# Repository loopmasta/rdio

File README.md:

# rdio

**rdio** turns your iPhone into a VHF/UHF radio. It connects to one or more ESP32-powered devices equipped with radio modules over Wi-Fi. Listen to transmissions, talk with push-to-talk, save your favourite channels and repeaters, and exchange APRS messages in a familiar chat-style interface.

<table>
  <tr>
    <td align="center"></td>
    <td align="center"></td>
    <td align="center"></td>
    <td align="center"></td>
    <td align="center"></td>
  </tr>
  <tr>
    <td align="center">Main screen</td>
    <td align="center">Transmit</td>
    <td align="center">APRS chat</td>
    <td align="center">Channel editor</td>
    <td align="center">Settings</td>
  </tr>
</table>

## How it works

- The ESP32 opens its own Wi-Fi network (or joins one you configure). The phone connects to it and talks to the radio over a WebSocket. Radios on a shared network are found automatically (Bonjour), so one app can control several of them.
- Receive audio goes from the radio to the phone as 16 kHz mono PCM. Transmit audio goes the other way while you hold the push-to-talk button.
- The module is tuned, squelched and keyed by the ESP32 through its UART and PTT lines, and a further line sets its transmit power.
- Bluetooth is not used.

## Features

- **Receive and transmit** in the selected band (VHF 134–174 MHz or UHF 400–480 MHz).
- **Channel list** with simplex and duplex (repeater) entries, shift direction and offset, CTCSS transmit and receive tones, and a 1750 Hz tone burst. Reorder by dragging, swipe to edit or delete.
- **APRS** on 1200 baud AFSK: the app decodes received packets (positions, Mic-E, messages, status) on APRS channels, shows them as a chat with distance and a link to Maps, links call signs to QRZ.com. You can also send: type a message in the chat to a call sign or to CQ. Messages to a station are repeated until it acknowledges them, the app acknowledges messages addressed to you, and everything is sent only while the channel is clear. A periodic position beacon is available too.
- **Several radios:** each radio announces itself on the network as a Bonjour service (`_rdio._tcp`, with its name, module type and firmware version). The app lists the radios it finds in Settings → Radio and switches between them with one tap. Give every radio its own name (Settings → Radio Name), because the name is also its Wi-Fi and host name.
- **Phone microphone chain** with a compressor and a mic level setting, the radio limits the transmit level so the deviation cannot be exceeded.
- **Native iOS design**: system controls, Light and Dark Mode, Dynamic Type, VoiceOver, haptics, no navigation bar.
- **Transmit safety**: the app only transmits inside the selected band, and the firmware releases the push-to-talk line when the connection drops, when no audio arrives, and after 120 seconds. Only one client can transmit.
- **Transmit power:** high (1 W) or low (0.5 W) with a switch in Settings → Radio. The radio remembers the choice; low power draws about half as much from the battery while transmitting.
- Firmware updates over Wi-Fi.

## Status

Working on a real radio: receive, transmit, channel handling, tones, tone burst, APRS decoding, and the APRS position beacon (tested over the air).

Not done yet: a scan function in the app.

The carrier board below is designed and routed; its [README](hardware/radio/README.md) lists the checks it passes and what is still to be verified at the bench. The harmonic filters below are **designed but not built or measured yet**. They are simulated only; check them with a NanoVNA before relying on them.

## Hardware

Everything is KiCad 10 and is generated by scripts, so the boards can be rebuilt and changed in code.

### Carrier board

A 57.4 × 26.0 mm two-layer board for an ESP32 38-pin DevKit (NodeMCU-32S style) and an SA818S / DRA818 module. The DevKit sits on top of the board plugged onto two 19-pin headers soldered into it from the bottom, the radio module sits on the bottom side, and an SMA jack on the end opposite the DevKit's USB port carries the antenna signal on a short track. There are two footprints for the jack, an edge-mount one and a right-angle one on top of the board; you fit one of them. Design files, parts and notes: [hardware/radio/README.md](hardware/radio/README.md).

<table>
  <tr>
    <td align="center"></td>
    <td align="center"></td>
  </tr>
  <tr>
    <td align="center">Top: DevKit (the audio and supply parts are under it), SMA jack</td>
    <td align="center">Bottom: radio module, SMA jack, DevKit pin rows</td>
  </tr>
</table>

| Function | ESP32 pin |
|---|---|
| Module UART (RX / TX) | GPIO16 / GPIO17 |
| PTT (low = transmit) | GPIO21, with a 10 k pull-up to 3.3 V |
| Squelch in | GPIO22 |
| High / low power | GPIO19 (open drain: the firmware pulls it low for 0.5 W and releases it for 1 W; it never drives it high) |
| RX audio in (ADC) | GPIO34, through a coupling capacitor and a 1.65 V bias divider |
| TX audio out | GPIO25, through an attenuator of about 1/100 |
| Power down | none: the module's power-down pin is tied to 3.3 V |

- The module's supply pin is fed from the DevKit's VIN pin (5 V from its USB-C) through a 0 Ω link, with a 220 µF and a 100 nF capacitor next to the module. The module draws up to 0.75 A while transmitting at high power, so use a 5 V source that can deliver at least 1 A (2 A is better) and check the voltage on the DevKit's VIN pin before the first power-up.
- Pin numbers and the antenna end are printed on the bottom silkscreen inside the module outline, to help with placing it.
- Connect an antenna or a dummy load before the first transmission and start the bench tests at low power. Details and the open points: [hardware/radio/README.md](hardware/radio/README.md).

### Harmonic filters (2 m and 70 cm)

Two small all-SMD low-pass filters (7th-order Chebyshev, 0.1 dB ripple, 50 Ω) that go between the board's SMA jack and the antenna and cut the radio module's harmonics. Details, simulation and parts notes: [hardware/filter/README.md](hardware/filter/README.md).

<table>
  <tr>
    <td align="center"></td>
    <td align="center"></td>
  </tr>
  <tr>
    <td align="center">2 m, 144–146 MHz</td>
    <td align="center">70 cm, 430–440 MHz</td>
  </tr>
</table>

| | 2 m | 70 cm |
|---|---|---|
| Passband | 144–146 MHz | 430–440 MHz |
| Insertion loss (simulated) | 0.56 dB | 0.50 dB |
| 2nd harmonic (simulated) | 52 dB down | 63 dB down |
| Board size | 38.6 × 12.4 mm | 35.0 × 12.4 mm |

### Ordering the boards

Gerber, drill, bill of materials and placement files for JLCPCB are in [hardware/jlcpcb/](hardware/jlcpcb/README.md): `radio/` for the carrier board and `filters/vhf`, `filters/uhf` for the filters. Check the LCSC part numbers in the bills of materials against JLCPCB's parts library before you order; the filter boards have none yet, because their inductors are still to be chosen. The electrolytic capacitors, the SMA connectors, the DevKit headers and the radio module are soldered by hand.

## Legal

Transmitting needs an amateur radio licence and must follow the rules that apply to you. The app limits the transmit frequency to the selected band, but you are responsible for staying within your licence and the local regulations.

**Privacy:** the app has no accounts, analytics or tracking. See the [privacy policy](https://loopmasta.github.io/rdio/privacy/).

## Repository contents

This repository lets a small group of testers order the hardware, build it and install the app, with no software knowledge or development tools. It holds the hardware design (`hardware/`), the screenshots (`docs/`) and this description.

The software is not included and does not need to be built:

- **iOS app:** the new version is not available yet, so there is no download link at the moment.
- **Firmware:** not published here. The web flasher has been removed, so there is no browser installer for the firmware at the moment.

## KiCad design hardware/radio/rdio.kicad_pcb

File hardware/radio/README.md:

# rdio carrier board

A 57.4 × 26.0 mm two-layer board that joins an ESP32 38-pin DevKit (NodeMCU-32S style) and an SA818S / DRA818 radio module. KiCad 10; the schematic and the board are generated by the scripts in [tools/](tools/README.md), so they can be changed in code.

- The DevKit sits **on top of** the thin carrier board, component side up. It plugs, with the 2.5 mm sockets built into it, onto two 19-pin headers (5 mm high) that are soldered into plated holes in the carrier from the bottom side.
- The radio module sits on the **bottom** side, between the two pin rows. It is mounted turned by 180° so that its antenna pad faces the SMA connector.
- The antenna connector is at the end where the DevKit's Wi-Fi antenna is, opposite the DevKit's USB port. The silkscreen says `ANT end (SMA side)` and `USB end (DevKit above)`. **Two connector footprints share that spot, and you fit one of them:**
  - **J2**, SMA edge connector (KooingTech SMA-KE, female, for 1.6 mm boards): sits on the board edge, the barrel points straight out of the board.
  - **J3**, right-angle SMA jack (BAT Wireless BWSMA-KWE-Z001, LCSC C496551, through hole): stands on the top side of the board, the barrel points out over the board edge. Its pads overlap those of J2, so never fit both.
- The small parts are on the top side, in the 7–8 mm gap between the carrier and the DevKit.

*3D render of the carrier board seen from the top (DevKit side). The DevKit and the radio module (on the bottom) are not shown. C8, FB1 and the J2 footprint are not fitted in the default build; C8 and FB1 are visible here.*

## Connections

| Module (SA818S) | Signal | ESP32 | Notes |
|---|---|---|---|
| 16 RXD | UART to the module | GPIO17 (UART2 TX) | 9600 baud, AT commands |
| 17 TXD | UART from the module | GPIO16 (UART2 RX) | connected directly, no series resistor |
| 5 PTT | transmit request | GPIO21 | low = transmit; **10 k pull-up to 3.3 V**, so a floating, crashed or resetting ESP32 means receive |
| 6 PD | power down | none | tied to 3.3 V: the module is always on |
| 7 H/L | power level | GPIO19 | open drain, low = low power (0.5 W), released = high power (1 W). **Never drive it high, never tie it to a supply.** |
| 1 SQ | squelch / carrier detect | GPIO22 | input, connected directly |
| 3 AF_OUT | receive audio | GPIO34 (ADC) | 1 µF coupling capacitor into a 100 k / 100 k divider (1.65 V bias) |
| 18 MIC_IN | transmit audio | GPIO25 (DAC) | 1 µF, then 100 k in series, 1 k to ground with 33 nF across it: about 1/100 attenuation, corner near 4.8 kHz |
| 12 ANT | antenna | SMA | 0.8 mm trace, drawn by hand |
| 8 VBAT, 9 / 10 GND | supply | | see Power |

GPIO26 and the other pins of the DevKit are not used.

## Power

- The module's VBAT comes from the DevKit's VIN pin (5 V from the DevKit's own USB-C) through R9, a 0 Ω link. The module accepts 3.3 to 5.5 V (the RF power is specified at 4.0 V).
- At the module: C6 100 µF, 16 V (6.3 mm can, 5.4 mm high; the board has the 6.3 × 5.8 mm footprint, which fits it; 220 µF was not available at 16 V) and C7 100 nF. On the 3.3 V side: C2 100 µF and C3 100 nF.
- **FB1 (ferrite bead) and C8 (100 µF) are not fitted.** To try them, fit both and remove R9: the bead keeps current steps of the module (power level change, PTT) away from the ESP32's regulator. Build without them first and see whether Wi-Fi still drops when the power level switches.
- The module draws about 60 mA receiving, 650–750 mA transmitting at high power and 450–550 mA at low power (datasheet). All of it passes through the DevKit's USB path and its VIN pin. Use a 5 V source that can deliver at least 1 A (2 A is better), and check the DevKit's input protection. USB 500 mA from a computer can brown out during a high-power transmission.
- Do not power the module from the DevKit's 3.3 V pin. Check the DevKit's behaviour before connecting USB and an external 5 V supply at the same time.

## Building and first power-up

1. Solder two 19-pin headers (5 mm high) into the carrier from the bottom side, then plug the DevKit onto them.
2. Place the SA818S on the bottom side with its antenna pad towards the SMA connector. Pin numbers 1 to 18 are printed inside the module outline, and an open ring marks the ring on the top of the module: put the module's ring over the board's ring.
3. Solder the antenna connector by hand: J2 (edge mount) or J3 (right angle on top), not both.
4. Connect a 50 Ω antenna or a dummy load **before the first transmission**, keep the antenna away from the DevKit's antenna and the audio wiring, and start the bench tests at low power. Transmitting needs the right amateur radio licence and an allowed frequency.

Gerber, drill, bill of materials and placement files for JLCPCB are in [../jlcpcb/radio/](../jlcpcb/README.md).

## Design status

The board is routed with Freerouting. KiCad's design rule check (with the project's rules, and also with 0.2 mm clearance, 0.3 mm copper-to-edge and 0.5 mm hole-to-hole) reports no unconnected items, no clearance errors, no shorts and no dangling tracks. What remains:

- the schematic symbol has a pin 11 (NC) that the footprint does not draw as a pad, which is harmless,
- the schematic check warns that the `VBAT` power symbol and the `Board` symbol library are not found, because the folder has no symbol library table,
- J2 (edge-mount SMA) has pads 0.25 mm from the board edge by design; it is not fitted in the default build.

## Still to verify at the bench

1. The typical-application schematic on pages 4 and 5 of the datasheet (the coupling into MIC_IN and the bias on AF_OUT) against the values above.
2. The idle and active voltage levels of pin 1.
3. The AF_OUT amplitude (peak or peak to peak) at each module volume setting.
4. The MIC_IN impedance, then change R4 (1 k) so that a 1750 Hz tone gives the right deviation (about 3 kHz), checked on a receiver or an SDR.

## Known limitations

- The antenna on the SMA connector is at the same end as the DevKit's Wi-Fi antenna, so a whip on the connector sits a few centimetres from it. A short coax pigtail, or an antenna mounted away from the board, helps more than any copper.
- Two RF filters were left out on purpose: 47–100 pF across R4 (2.4 GHz pickup into MIC_IN) and small series resistors and capacitors on the control lines (433 MHz pickup). The circuit is as shown.
- The 3D models are simple placeholders, not accurate models.

More details (footprints, the SMA connector, the shielding by copper pours, and a 4-layer variant): [design-notes.md](design-notes.md).

## Files

| File | What it is |
|---|---|
| `rdio.kicad_pro`, `rdio.kicad_sch`, `rdio.kicad_pcb` | the KiCad project, schematic and board |
| `rdio_schematic.pdf` | the schematic as a PDF |
| `rdio.pretty/`, `rdio.3dshapes/`, `fp-lib-table` | footprints (SA818S, DevKit header holes, SMA edge connector J2, right-angle SMA J3) and their 3D models |
| `rdio.kicad_dru` | custom DRC rules: J2 and J3 are alternatives, so their overlapping courtyards are not reported |
| `tools/` | the scripts that generate the schematic and the board, see [tools/README.md](tools/README.md) |
| `SA818S V1.8.pdf`, `NodeMCU ESP32S 38pin.png` | the module's datasheet and a picture of the DevKit |
| `design-notes.md` | design notes |

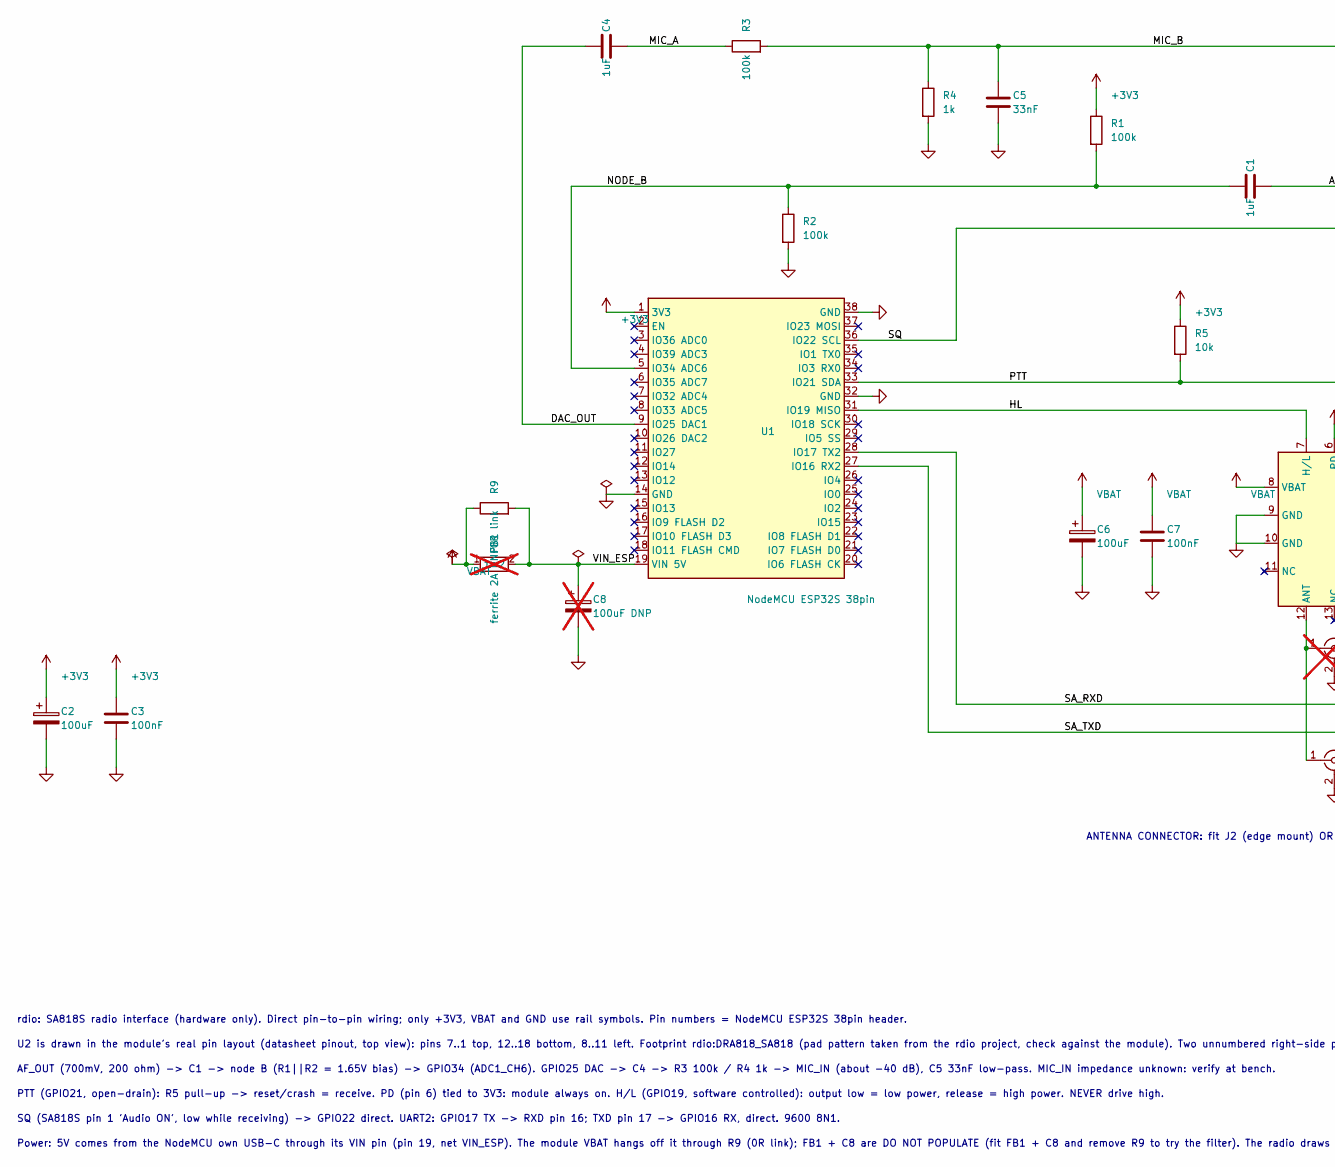
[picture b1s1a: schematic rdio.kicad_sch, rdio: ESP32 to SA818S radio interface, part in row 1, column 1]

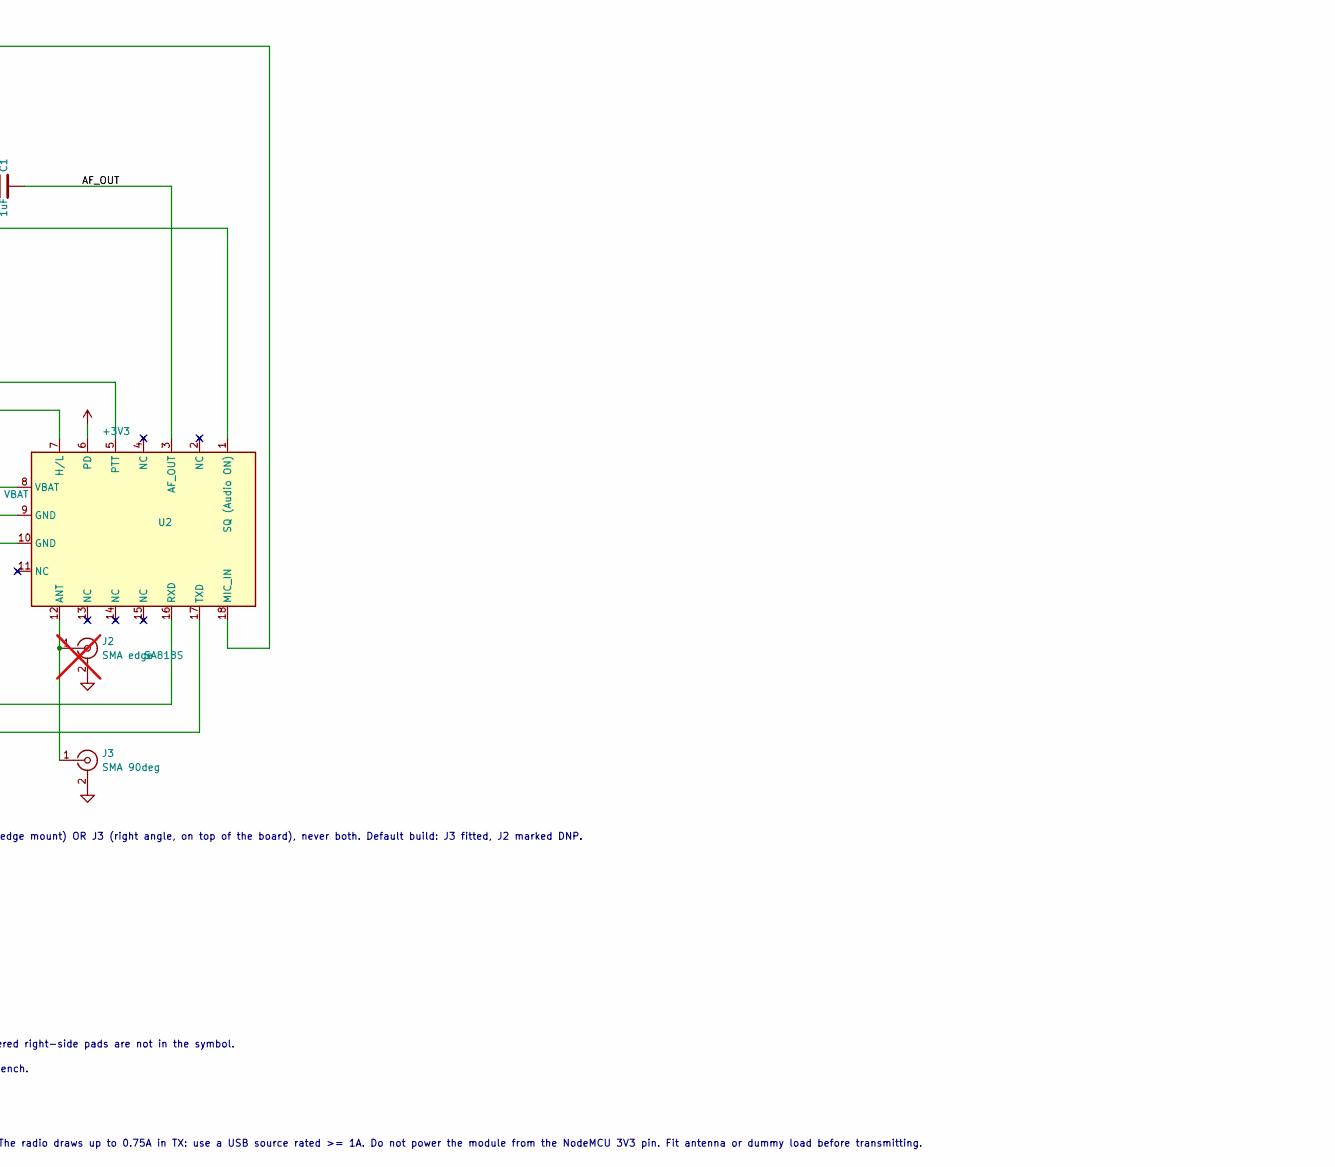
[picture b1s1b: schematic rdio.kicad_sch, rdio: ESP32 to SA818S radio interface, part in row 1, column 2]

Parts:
C1, C4: 1uF; C_0603_1608Metric
C2: 100uF; CP_Elec_6.3x5.4
C3, C7: 100nF; C_0603_1608Metric
C5: 33nF; C_0603_1608Metric
C6: 100uF; CP_Elec_6.3x5.8
C8: 100uF DNP; CP_Elec_6.3x5.4; not fitted
FB1: ferrite 2A DNP; L_0805_2012Metric; not fitted
J2: SMA edge; SMA_KooingTech_SMA-KE_EdgeMount; not fitted
J3: SMA 90deg; SMA_BAT_Wireless_BWSMA-KWE-Z001
R1, R2, R3: 100k; R_0603_1608Metric
R4: 1k; R_0603_1608Metric
R5: 10k; R_0603_1608Metric
R9: 0R link; R_0603_1608Metric
U1: NodeMCU ESP32S 38pin; ESP32_DevKit_38pin_PinHoles
U2: SA818S; DRA818_SA818

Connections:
+3V3: C2.1, C3.1, R1.1, R5.1, U1.1 (3V3), U2.6 (PD)
/AF_OUT: C1.2, U2.3 (AF_OUT)
/DAC_OUT: C4.1, U1.9 (IO25 DAC1)
/HL: U1.31 (IO19 MISO), U2.7 (H/L)
/MIC_A: C4.2, R3.1
/MIC_B: C5.1, R3.2, R4.1, U2.18 (MIC_IN)
/NODE_B: C1.1, R1.2, R2.1, U1.5 (IO34 ADC6)
/PTT: R5.2, U1.33 (IO21 SDA), U2.5 (PTT)
/SA_RXD: U1.28 (IO17 TX2), U2.16 (RXD)
/SA_TXD: U1.27 (IO16 RX2), U2.17 (TXD)
/SQ: U1.36 (IO22 SCL), U2.1 (SQ (Audio ON))
/VIN_ESP: C8.1, FB1.2, R9.2, U1.19 (VIN 5V)
GND: C2.2, C3.2, C5.2, C6.2, C7.2, C8.2, J2.2 (Ext), J3.2 (Ext), R2.2, R4.2, U1.14 (GND), U1.32 (GND), U1.38 (GND), U2.9 (GND), U2.10 (GND)
unnamed: J2.1 (In), J3.1 (In), U2.12 (ANT)
VBAT: C6.1, C7.1, FB1.1, R9.1, U2.8 (VBAT)

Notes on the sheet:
rdio: SA818S radio interface (hardware only). Direct pin-to-pin wiring; only +3V3, VBAT and GND use rail symbols. Pin numbers = NodeMCU ESP32S 38pin header.
U2 is drawn in the module's real pin layout (datasheet pinout, top view): pins 7..1 top, 12..18 bottom, 8..11 left. Footprint rdio:DRA818_SA818 (pad pattern taken from the rdio project, check against the module). Two unnumbered right-side pads are not in the symbol.
AF_OUT (700mV, 200 ohm) -> C1 -> node B (R1||R2 = 1.65V bias) -> GPIO34 (ADC1_CH6). GPIO25 DAC -> C4 -> R3 100k / R4 1k -> MIC_IN (about -40 dB), C5 33nF low-pass. MIC_IN impedance unknown: verify at bench.
PTT (GPIO21, open-drain): R5 pull-up -> reset/crash = receive. PD (pin 6) tied to 3V3: module always on. H/L (GPIO19, software controlled): output low = low power, release = high power. NEVER drive high.
SQ (SA818S pin 1 'Audio ON', low while receiving) -> GPIO22 direct. UART2: GPIO17 TX -> RXD pin 16; TXD pin 17 -> GPIO16 RX, direct. 9600 8N1.
Power: 5V comes from the NodeMCU own USB-C through its VIN pin (pin 19, net VIN_ESP). The module VBAT hangs off it through R9 (0R link); FB1 + C8 are DO NOT POPULATE (fit FB1 + C8 and remove R9 to try the filter). The radio draws up to 0.75A in TX: use a USB source rated >= 1A. Do not power the mod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
ANTENNA CONNECTOR: fit J2 (edge mount) OR J3 (right angle, on top of the board), never both. Default build: J3 fitted, J2 marked DNP.

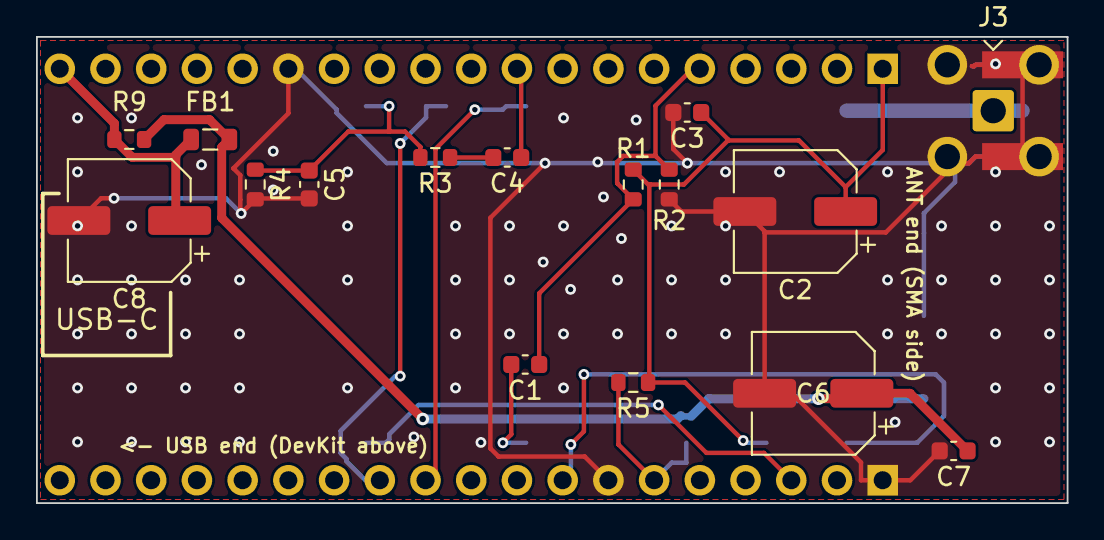
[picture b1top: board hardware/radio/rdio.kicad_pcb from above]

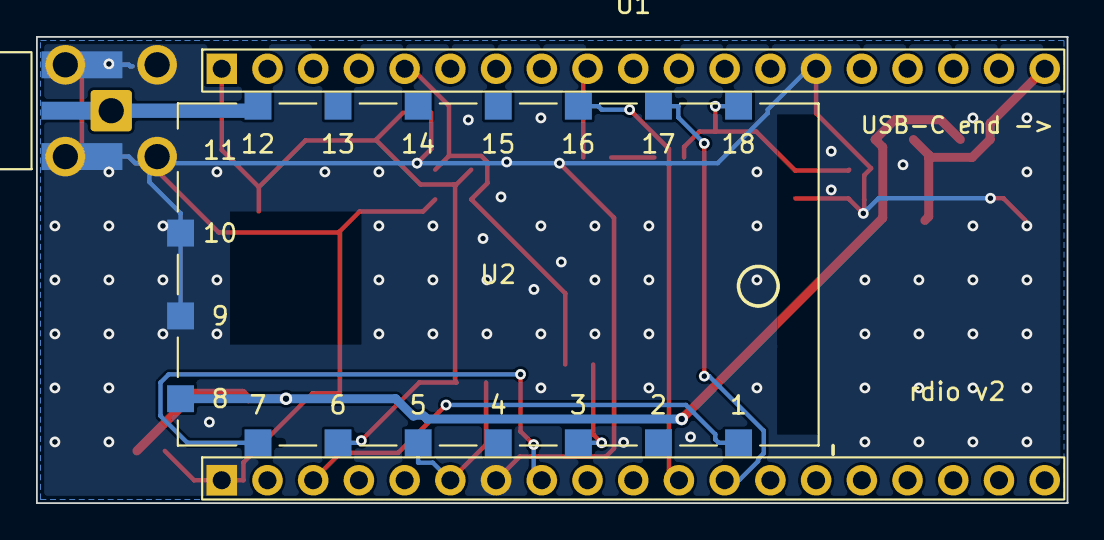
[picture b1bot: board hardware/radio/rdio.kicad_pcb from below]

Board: 2 copper layers, 57.3 x 25.9 mm, 19 parts (3 on the bottom side), 15 nets.

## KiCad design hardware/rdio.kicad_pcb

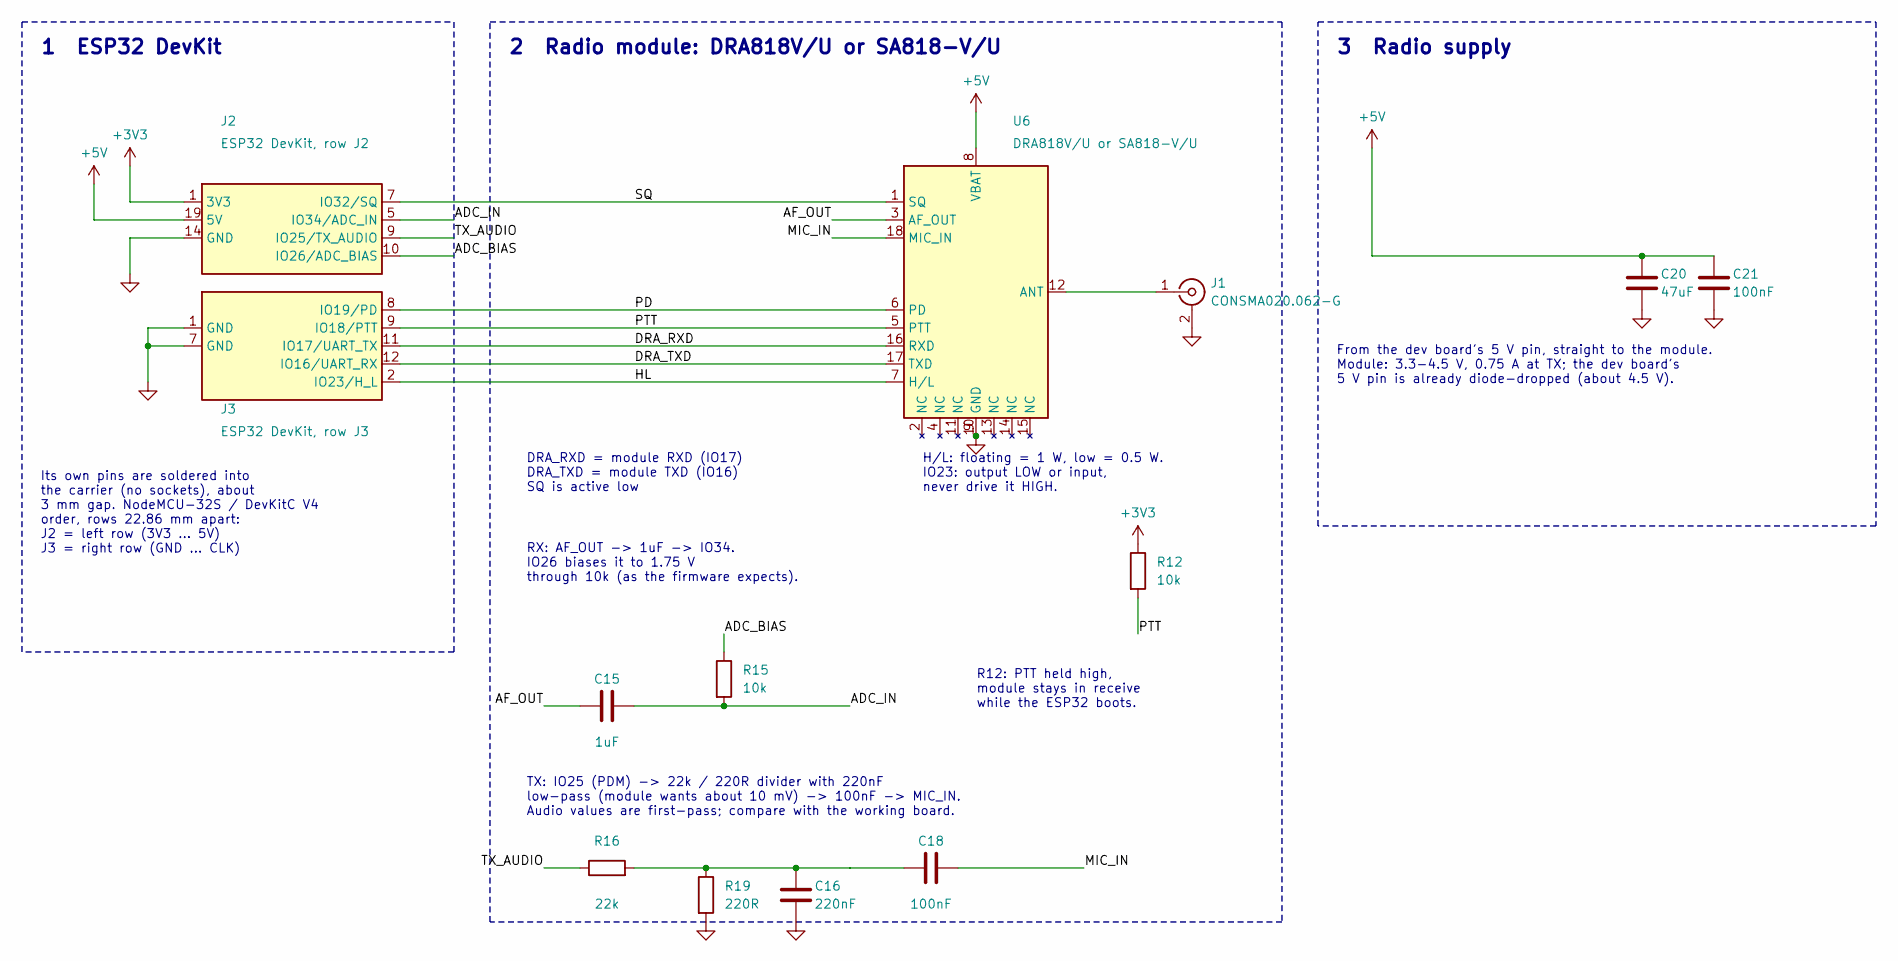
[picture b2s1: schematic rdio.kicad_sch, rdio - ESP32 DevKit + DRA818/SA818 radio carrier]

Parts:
C15: 1uF; C_0603_1608Metric
C16: 220nF; C_0603_1608Metric
C18, C21: 100nF; C_0603_1608Metric
C20: 47uF; C_1206_3216Metric
J1: CONSMA020.062-G; CONSMA020_062_G
J2: ESP32 DevKit, row J2; PinHoles_1x19_P2.54mm
J3: ESP32 DevKit, row J3; PinHoles_1x19_P2.54mm
R12, R15: 10k; R_0603_1608Metric
R16: 22k; R_0603_1608Metric
R19: 220R; R_0603_1608Metric
U6: DRA818V/U or SA818-V/U; DRA818_SA818

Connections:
+3V3: J2.1 (3V3), R12.1
+5V: C20.1, C21.1, J2.19 (5V), U6.8 (VBAT)
/ADC_BIAS: J2.10 (IO26/ADC_BIAS), R15.1
/ADC_IN: C15.2, J2.5 (IO34/ADC_IN), R15.2
/AF_OUT: C15.1, U6.3 (AF_OUT)
/DRA_RXD: J3.11 (IO17/UART_TX), U6.16 (RXD)
/DRA_TXD: J3.12 (IO16/UART_RX), U6.17 (TXD)
/HL: J3.2 (IO23/H_L), U6.7 (H/L)
/MIC_IN: C18.2, U6.18 (MIC_IN)
/PD: J3.8 (IO19/PD), U6.6 (PD)
/PTT: J3.9 (IO18/PTT), R12.2, U6.5 (PTT)
/SQ: J2.7 (IO32/SQ), U6.1 (SQ)
/TX_AUDIO: J2.9 (IO25/TX_AUDIO), R16.1
GND: C16.2, C20.2, C21.2, J1.2 (Ext), J2.14 (GND), J3.1 (GND), J3.7 (GND), R19.2, U6.9 (GND), U6.10 (GND)
unnamed: C16.1, C18.1, R16.2, R19.1
unnamed: J1.1 (In), U6.12 (ANT)

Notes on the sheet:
1 ESP32 DevKit
Its own pins are soldered into the carrier (no sockets), about 3 mm gap. NodeMCU-32S / DevKitC V4 order, rows 22.86 mm apart: J2 = left row (3V3 ... 5V) J3 = right row (GND ... CLK)
2 Radio module: DRA818V/U or SA818-V/U
DRA_RXD = module RXD (IO17) DRA_TXD = module TXD (IO16) SQ is active low
H/L: floating = 1 W, low = 0.5 W. IO23: output LOW or input, never drive it HIGH.
R12: PTT held high, module stays in receive while the ESP32 boots.
RX: AF_OUT -> 1uF -> IO34. IO26 biases it to 1.75 V through 10k (as the firmware expects).
TX: IO25 (PDM) -> 22k / 220R divider with 220nF low-pass (module wants about 10 mV) -> 100nF -> MIC_IN. Audio values are first-pass; compare with the working board.
3 Radio supply
From the dev board's 5 V pin, straight to the module. Module: 3.3-4.5 V, 0.75 A at TX; the dev board's 5 V pin is already diode-dropped (about 4.5 V).

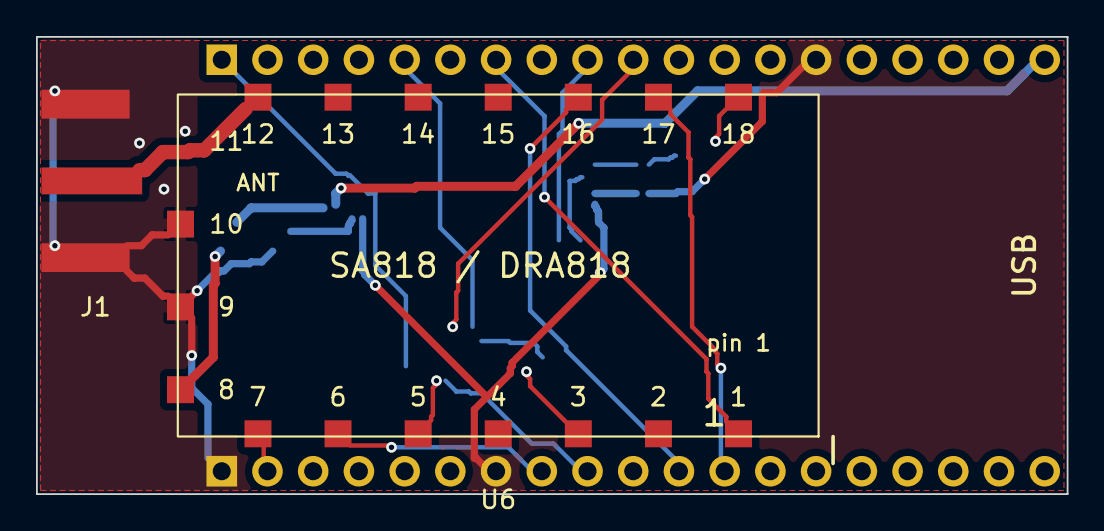
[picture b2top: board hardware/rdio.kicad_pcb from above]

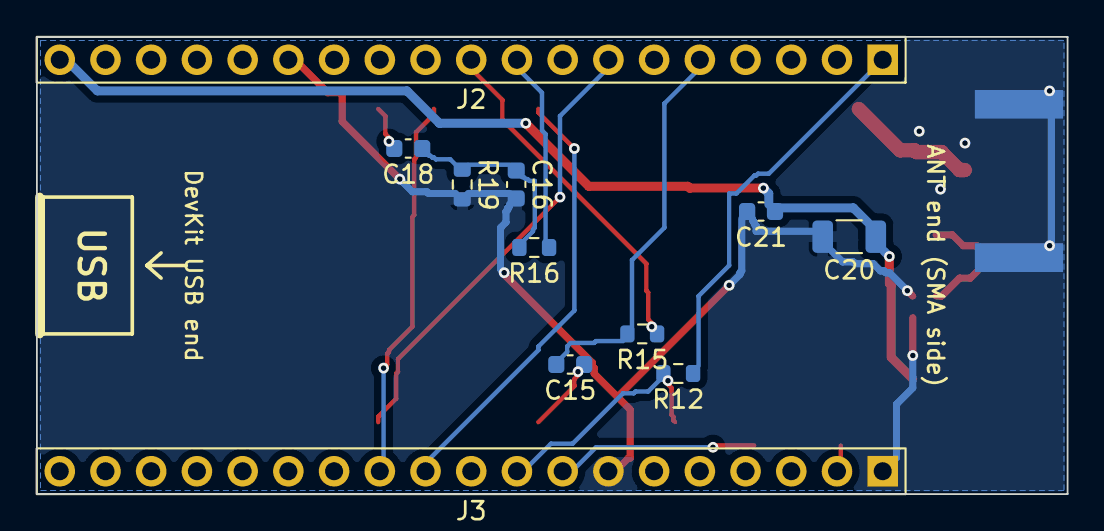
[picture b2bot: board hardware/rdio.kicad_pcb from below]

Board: 2 copper layers, 57.3 x 25.4 mm, 14 parts (11 on the bottom side), 16 nets.

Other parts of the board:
DK1: ESP32_DevKit_38pin

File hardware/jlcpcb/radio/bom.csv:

Comment,Designator,Footprint,LCSC Part #
1uF,C15,C_0603_1608Metric,C15849
220nF,C16,C_0603_1608Metric,C23630
100nF,"C18,C21",C_0603_1608Metric,C14663
47uF,C20,C_1206_3216Metric,C96123
10k,"R12,R15",R_0603_1608Metric,C25804
22k,R16,R_0603_1608Metric,C31850
220R,R19,R_0603_1608Metric,C22962

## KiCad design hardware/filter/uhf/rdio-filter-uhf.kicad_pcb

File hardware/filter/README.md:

# Harmonic filters for the radio (2 m and 70 cm)

Two small all-SMD low-pass filters. Each goes between the carrier board's SMA connector and the antenna and cuts the
radio module's harmonics (the second harmonic is the one that matters). 7th-order Chebyshev (0.1 dB ripple), 50 ohm,
shunt-C first: C1 - L1 - C2 - L2 - C3 - L3 - C4. SMA in on one end, SMA out on the other, solid ground on both layers.

| | 2 m (`vhf/`) | 70 cm (`uhf/`) |
|---|---|---|
| Passband | 144-146 MHz | 430-440 MHz |
| Filter edge (0.1 dB) | 155 MHz | 460 MHz |
| C1 = C4 | 22 pF | 8.2 pF |
| L1 = L3 | 68 nH | 22 nH |
| C2 = C3 | 39 pF | 13 pF |
| L2 | 82 nH | 27 nH |
| Capacitors | C0G/NP0, 0402, 50 V | C0G/NP0, 0402, 50 V |
| Inductors | high-Q chip, 0603 | high-Q chip, 0402 |
| Board size | 38.6 x 12.4 mm | 35.0 x 12.4 mm |
| Insertion loss (simulated) | 0.56 dB | 0.50 dB |
| Return loss in band (simulated) | 36 dB | 27 dB |
| 2nd harmonic (simulated) | 52 dB down | 63 dB down |
| Worst case, 5 % parts, 500 runs | 0.77 dB loss, 50 dB at 2nd harmonic | 0.75 dB loss, 60 dB at 2nd harmonic |

Simulated response of the two filters:

<table>
  <tr>
    <td align="center"></td>
    <td align="center"></td>
  </tr>
  <tr>
    <td align="center">2 m, 144–146 MHz</td>
    <td align="center">70 cm, 430–440 MHz</td>
  </tr>
</table>

## What is simulated and what is not

The simulation (`tools/filter_sim.py`, see below how to run it) includes inductor Q (70 / 90), the inductors' winding capacitance, capacitor ESL and
ESR, and component tolerance. It does not include the board: pad and via parasitics, coupling between neighbouring parts,
and the SMA transitions. The board is a straight 50-ohm line with the shunt capacitors going to ground vias right at their
pads, but it has not been measured. Expect a few percent shift in the filter edge. Measure S21 and S11 with a NanoVNA
before relying on it, and trim a capacitor by one step if the passband edge is off. The very high simulated attenuation at
the 3rd and 5th harmonics (85 dB and more) is not realistic on a real board; coupling limits it to roughly 60-70 dB.
This is a design aid, not a compliance measurement.

## Running the simulation

`tools/filter_sim.py` computes the ideal values, picks the E24 values, simulates the response with the part losses and runs the tolerance test. It needs numpy, which is not installed by default (`pip install --target /tmp/np numpy`). From the repository root:

    PYTHONPATH=/tmp/np python3 hardware/filter/tools/filter_sim.py

It prints the results shown above and rewrites `design.json` and the `*-response.svg` plots in `vhf/` and `uhf/` (the PNG versions are converted from the SVG files separately). Inductor Q, capacitor losses and the parasitics are set at the top of the script (`BANDS`).

## Rebuilding the schematics and the boards

The schematics, the connector footprints and 3D bodies, and the boards are generated, so a change in `design.json` (or in a layout number) can be carried through. From the repository root, with KiCad 10 installed:

    python3 -I hardware/filter/tools/gen_filter.py          # schematics, footprints, 3D bodies (reads design.json)
    for b in vhf uhf; do
      kicad-cli sch export netlist --format kicadxml -o hardware/filter/$b/rdio-filter-$b.net.xml hardware/filter/$b/rdio-filter-$b.kicad_sch
      /Applications/KiCad/KiCad.app/Contents/Frameworks/Python.framework/Versions/Current/bin/python3 hardware/filter/tools/gen_filter_pcb.py $b
    done
    python3 -I hardware/jlcpcb/gen_jlcpcb.py vhf uhf        # order files

`tools/sch_engine.py` is the schematic writer behind `gen_filter.py`. `gen_filter_pcb.py` lays the board out along a straight 50 Ω line: the connectors at the two ends, the series inductors in the line, each shunt capacitor with a ground via at its pad, ground pours on both layers and stitching vias. Both scripts honour `FILTER_DIR` to write somewhere else than `hardware/filter`. Regenerating the boards gives the same parts and positions as the files in this folder (checked against the committed boards: same positions, tracks and zones, and no DRC violations); the schematics get new UUIDs.

## Parts notes

- LCSC part numbers for the capacitors and inductors, the two parts that are still open, and what the inductor Q costs: [../jlcpcb/README.md](../jlcpcb/README.md).
- Check that the inductor values exist in the series you pick (for example Coilcraft 0603HP or Murata LQW18 for 68/82 nH,
  Coilcraft 0402HP or Murata LQW15 for 22/27 nH) and that the Q is at least 50 at the band.
- 0402 parts are small to hand-solder. The 0603 inductors on the 2 m board are easier.
- The shunt capacitors see about 7 V peak at 1 W; 50 V C0G is plenty.
- Connectors: `J1` (marked RADIO) is an SMA **male plug**, the threaded kind with a coupling nut, so it screws straight onto
  the carrier's SMA jack with no adapter. `J2` (marked ANTENNA) is the **TE/Linx CONSMA020.062-G** SMA jack (female, edge mount,
  for 0.062 in = 1.57 mm boards, 50 ohm, to 18 GHz). Its footprint (`rdio-filter.pretty/CONSMA020_062_G`) is built from the
  Linx drawing's "recommended footprint": RF pad 1.5 x 5.6 mm, four ground pads 1.6 x 4.9 mm at 4.26 mm (two on each layer),
  recessed 0.25 mm from the board edge to keep the copper-to-edge clearance. The 6.5 mm "mounting hole" in that drawing is a
  panel cut-out, not a PCB hole. The 3D bodies of both connectors are simple placeholders.
  The plug (`SMA_Plug_EdgeMount`) copies the pad pattern of the Amphenol edge-launch jack; use a plug whose datasheet matches it,
  or tell me the part and I will build its footprint from the datasheet.
  Order the boards 1.6 mm thick (the connector is specified for 1.57 mm).
  Open the filters as their own projects: `vhf/rdio-filter-vhf.kicad_pro` and `uhf/rdio-filter-uhf.kicad_pro`.
- The filter loses 0.5-0.8 dB (about 11-16 % of the power). That is the price of the harmonic rejection.

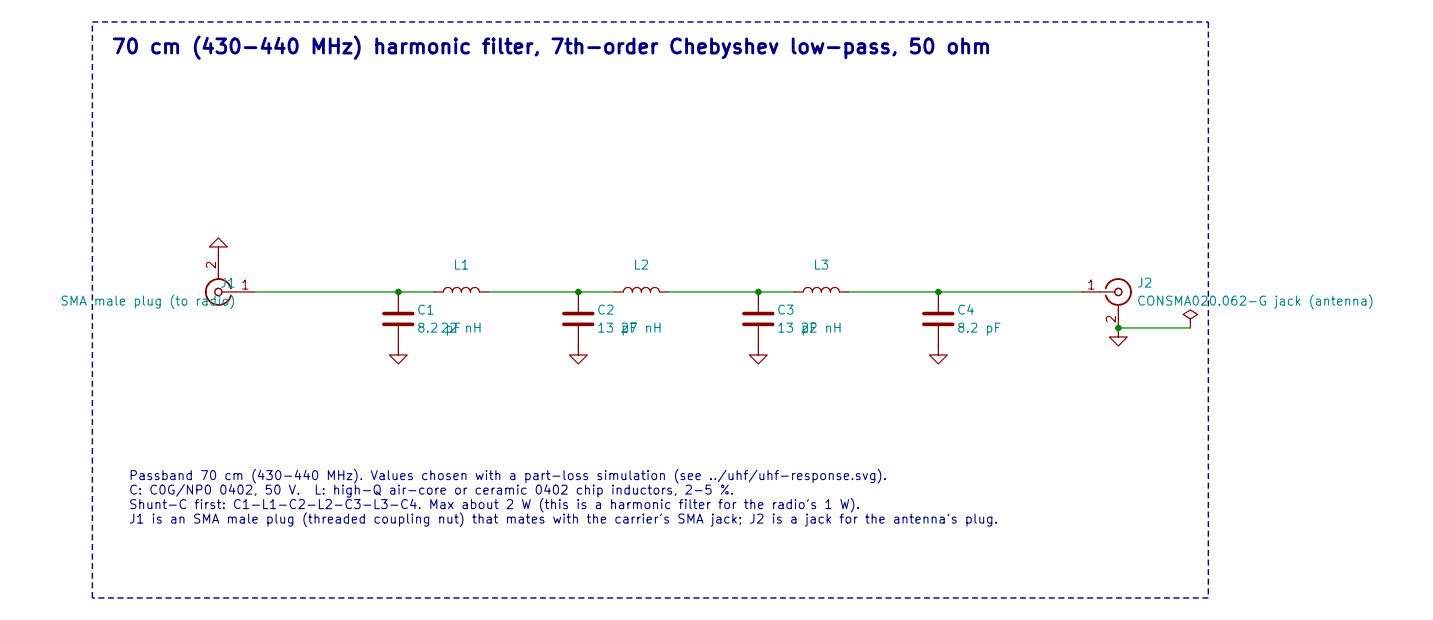
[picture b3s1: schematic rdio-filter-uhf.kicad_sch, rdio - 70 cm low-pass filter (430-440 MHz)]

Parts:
C1, C4: 8.2 pF; C_0402_1005Metric
C2, C3: 13 pF; C_0402_1005Metric
J1: SMA male plug (to radio); SMA_Plug_EdgeMount
J2: CONSMA020.062-G jack (antenna); CONSMA020_062_G
L1, L3: 22 nH; L_0402_1005Metric
L2: 27 nH; L_0402_1005Metric

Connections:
GND: C1.2, C2.2, C3.2, C4.2, J1.2 (Ext), J2.2 (Ext)
unnamed: C2.1, L1.2, L2.1
unnamed: C3.1, L2.2, L3.1
unnamed: C1.1, J1.1 (In), L1.1
unnamed: C4.1, J2.1 (In), L3.2

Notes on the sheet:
70 cm (430-440 MHz) harmonic filter, 7th-order Chebyshev low-pass, 50 ohm
Passband 70 cm (430-440 MHz). Values chosen with a part-loss simulation (see ../uhf/uhf-response.svg). C: C0G/NP0 0402, 50 V. L: high-Q air-core or ceramic 0402 chip inductors, 2-5 %. Shunt-C first: C1-L1-C2-L2-C3-L3-C4. Max about 2 W (this is a harmonic filter for the radio's 1 W). J1 is an SMA ma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

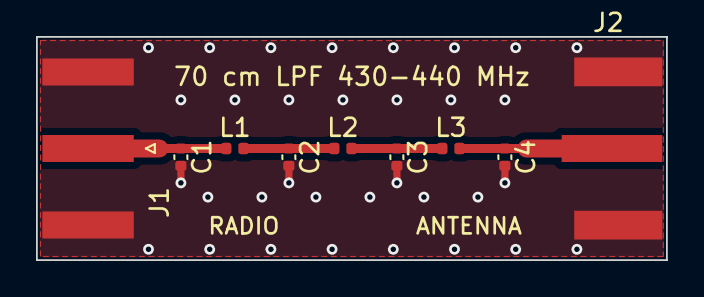
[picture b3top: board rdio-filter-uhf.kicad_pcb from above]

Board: 2 copper layers, 35.0 x 12.4 mm, 9 parts (0 on the bottom side), 5 nets.

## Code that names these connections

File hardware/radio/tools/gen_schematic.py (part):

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TOPX = {"7":-15.24,"6":-10.16,"5":-5.08,"4":0,"3":5.08,"2":10.16,"1":15.24}
BOTX = {"12":-15.24,"13":-10.16,"14":-5.08,"15":0,"16":5.08,"17":10.16,"18":15.24}
LEFTY = {"8":7.62,"9":2.54,"10":-2.54,"11":-7.62}
PIN = {"1":("SQ (Audio ON)","output"),"2":("NC","no_connect"),"3":("AF_OUT","output"),"4":("NC","no_connect"),
       "5":("PTT","input"),"6":("PD","input"),"7":("H/L","input"),"8":("VBAT","power_in"),"9":("GND","power_in"),
       "10":("GND","power_in"),"11":("NC","no_connect"),"12":("ANT","passive"),"13":("NC","no_connect"),
       "14":("NC","no_connect"),"15":("NC","no_connect"),"16":("RXD","input"),"17":("TXD","output"),"18":("MIC_IN","input")}
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wire(110.49,y,x,y); junc(121.92,y)
part("Board:FerriteBead","FB1","ferrite 2A DNP",106.68,y,90,dnp=True); wire(102.87,y,99.06,y); power("VBAT",99.06,y); power("PWR_FLAG",99.06,y)
part("Device:C_Polarized","C8","100uF DNP",121.92,182.88,dnp=True); wire(121.92,y,121.92,179.07); wire(121.92,186.69,121.92,191.77); power("GND",121.92,191.77)
label("VIN_ESP",124.46,y)
power("PWR_FLAG",121.92,y)
# 0 ohm link in parallel with FB1: fitted while FB1/C8 are not populated
junc(101.6,y); junc(113.03,y)
poly((101.6,y),(101.6,165.1),(102.87,165.1)); part("Device:R","R9","0R link",106.68,165.1,90); poly((110.49,165.1),(113.03,165.1),(113.03,y))

# analog in: AF_OUT (top pin 3) -> C1 -> node B -> GPIO34
XA = 120.65; AFY = 106.68
ax,ay = sa_pos("3")
x,y = P("5");  poly((x,y),(XA,y),(XA,AFY),(240.03,AFY))
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part("Device:R","R2","100k",160.02,114.3); wire(160.02,AFY,160.02,110.49); wire(160.02,118.11,160.02,120.65); power("GND",160.02,120.65)
part("Device:R","R1","100k",215.9,96.52);  wire(215.9,AFY,215.9,100.33); wire(215.9,92.71,215.9,88.9); power("+3V3",215.9,88.9)

# analog out: GPIO25 -> C4 -> R3 -> MIC_IN (bottom pin 18, reached on the right side of the module)
XB = 111.76; MICY = 81.28; XR = 292.1
mx,my = sa_pos("18")
x,y = P("9");  poly((x,y),(XB,y),(XB,MICY),(123.19,MICY))
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# SQ: GPIO22 -> top pin 1
sx,sy = sa_pos("1"); x,y = P("36")
poly((x,y),(190.5,y),(190.5,114.3),(sx,114.3),(sx,sy))
# PTT: GPIO21 -> top pin 5 (straight row), R5 pull-up
px,py = sa_pos("5"); x,y = P("33")
poly((x,y),(px,y),(px,py))
junc(231.14,y); wire(231.14,y,231.14,y-3.81); part("Device:R","R5","10k",231.14,y-7.62); wire(231.14,y-11.43,231.14,y-13.97); power("+3V3",231.14,y-13.97)
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notes = [
 "rdio: SA818S radio interface (hardware only). Direct pin-to-pin wiring; only +3V3, VBAT and GND use rail symbols. Pin numbers = NodeMCU ESP32S 38pin header.",
 "U2 is drawn in the module's real pin layout (datasheet pinout, top view): pins 7..1 top, 12..18 bottom, 8..11 left. Footprint rdio:DRA818_SA818 (pad pattern taken from the rdio project, check against the module). Two unnumbered right-side pads are not in the symbol.",
 "AF_OUT (700mV, 200 ohm) -> C1 -> node B (R1||R2 = 1.65V bias) -> GPIO34 (ADC1_CH6). GPIO25 DAC -> C4 -> R3 100k / R4 1k -> MIC_IN (about -40 dB), C5 33nF low-pass. MIC_IN impedance unknown: verify at bench.",
 "PTT (GPIO21, open-drain): R5 pull-up -> reset/crash = receive. PD (pin 6) tied to 3V3: module always on. H/L (GPIO19, software controlled): output low = low power, release = high power. NEVER drive high.",
 "SQ (SA818S pin 1 'Audio ON', low while receiving) -> GPIO22 direct. UART2: GPIO17 TX -> RXD pin 16; TXD pin 17 -> GPIO16 RX, direct. 9600 8N1.",
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]
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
